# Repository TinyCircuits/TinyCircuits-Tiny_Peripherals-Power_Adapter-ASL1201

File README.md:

# TinyCircuits TinyLily Mini Power Adapter
# ASL1201 Rev2

The design files are located under design_files/ for the TinyCircuits ASL1201 Rev 2 PCB.  This is a TinyLily Mini Power Adapter, that mates to the TinyLily Mini board and has a JST power connector, along with pads to solder to.

Format is in Cadsoft Eagle format - Eagle version 6.2 was used for the original design.

For more infomation on this, check out the product page at TinyCircuits.com: https://tinycircuits.com/collections/tinylily/products/tinylily-battery-adapter

# License:

Design by TinyCircuits.
All design files are released under the Creative Commons Attribution Share-Alike 3.0 License, see the following link for details: http://creativecommons.org/licenses/by-sa/3.0

All text above must be included in any redistribution or derived design

This project uses designs and concepts developed as part of the Arduino project and the LilyPad project.  The TinyCircuits design files themselves (schematics, PCB and libraries) are not directly derived from these works' design files and have been created new, however the concepts and basic architecture behind the TinyDuino and TinyLily products are derived and we thank the hard work of the organizations below for their contributions to open-source hardware:
  
Original Arduino Uno Design by Team Arduino

LilyPad Arduino Design by Leah Buechley and Sparkfun Electronics

Please support the open-source hardware community

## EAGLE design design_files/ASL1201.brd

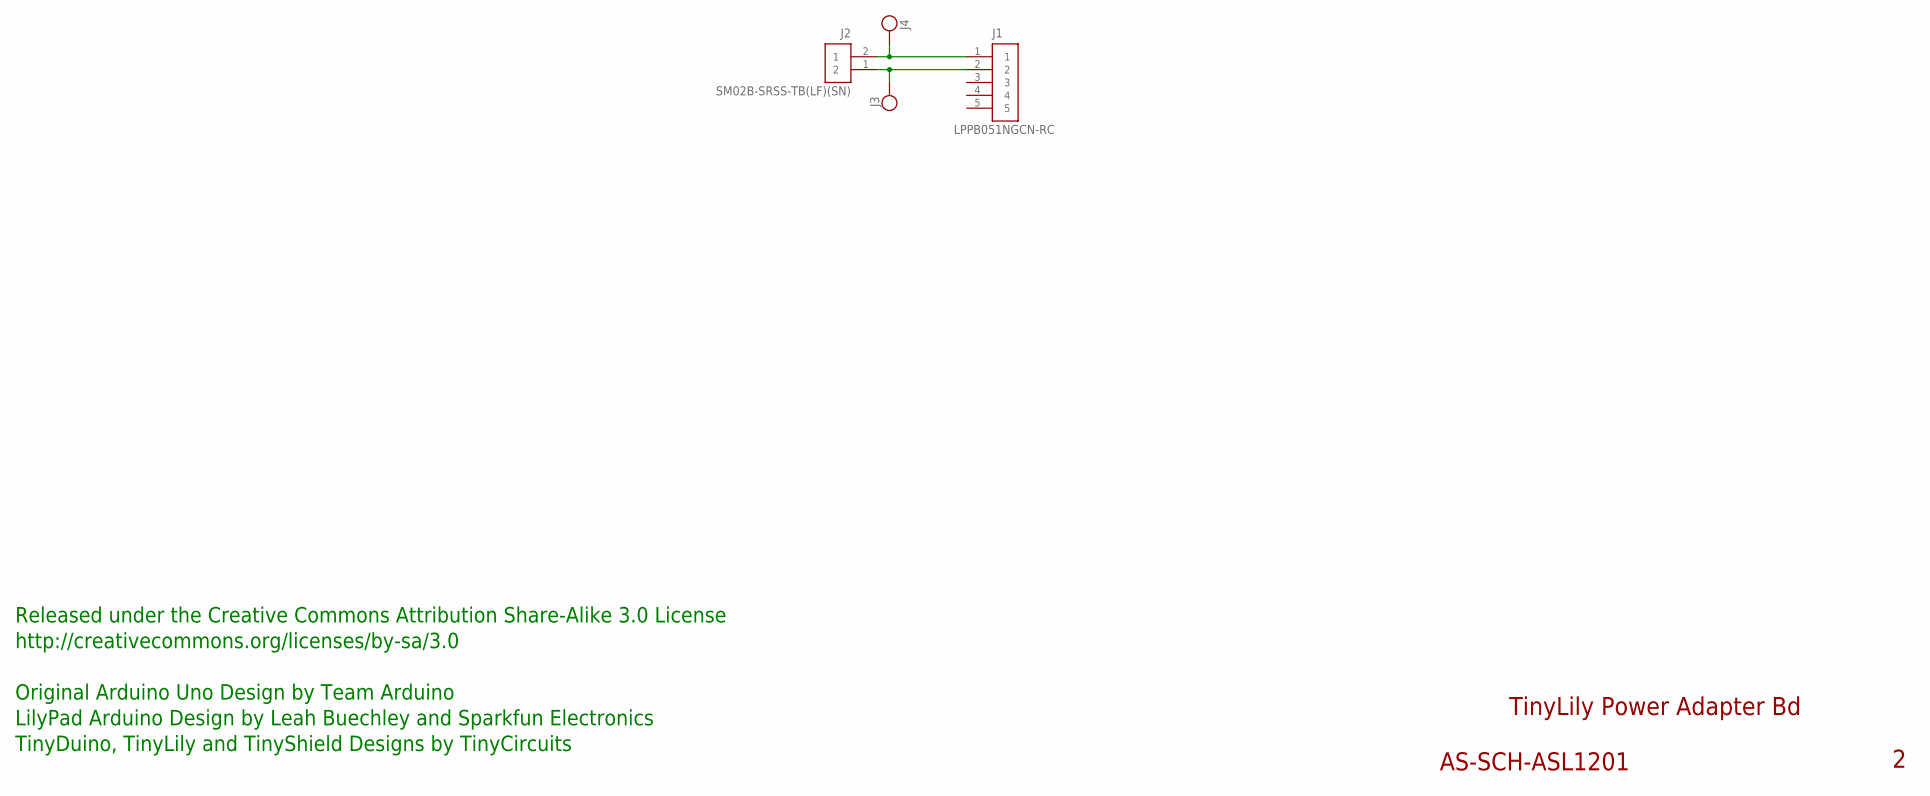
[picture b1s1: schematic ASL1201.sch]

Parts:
J1: LPPB051NGCN-RC; 1X5_.05_RA_TH_RECPT
J2: SM02B-SRSS-TB(LF)(SN); JST_SH_2X1
J3, J4: PIN_1X.1"1; 1X.1"_2

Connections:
unnamed: J1.1, J2.2 (1), J4.1
unnamed: J1.2, J2.1 (2), J3.1

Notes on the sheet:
TinyLily Power Adapter Bd
AS-SCH-ASL1201
Released under the Creative Commons Attribution Share-Alike 3.0 License
http://creativecommons.org/licenses/by-sa/3.0
LilyPad Arduino Design by Leah Buechley and Sparkfun Electronics
TinyDuino, TinyLily and TinyShield Designs by TinyCircuits
Original Arduino Uno Design by Team Arduino

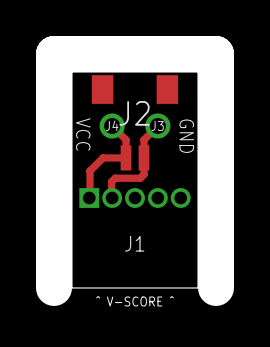
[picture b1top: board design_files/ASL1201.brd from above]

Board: 2 copper layers, 9.0 x 13.0 mm, 5 parts (0 on the bottom side), 2 nets.

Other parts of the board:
U$1: DOCFIELD-TINYCIRCUITS-PCB

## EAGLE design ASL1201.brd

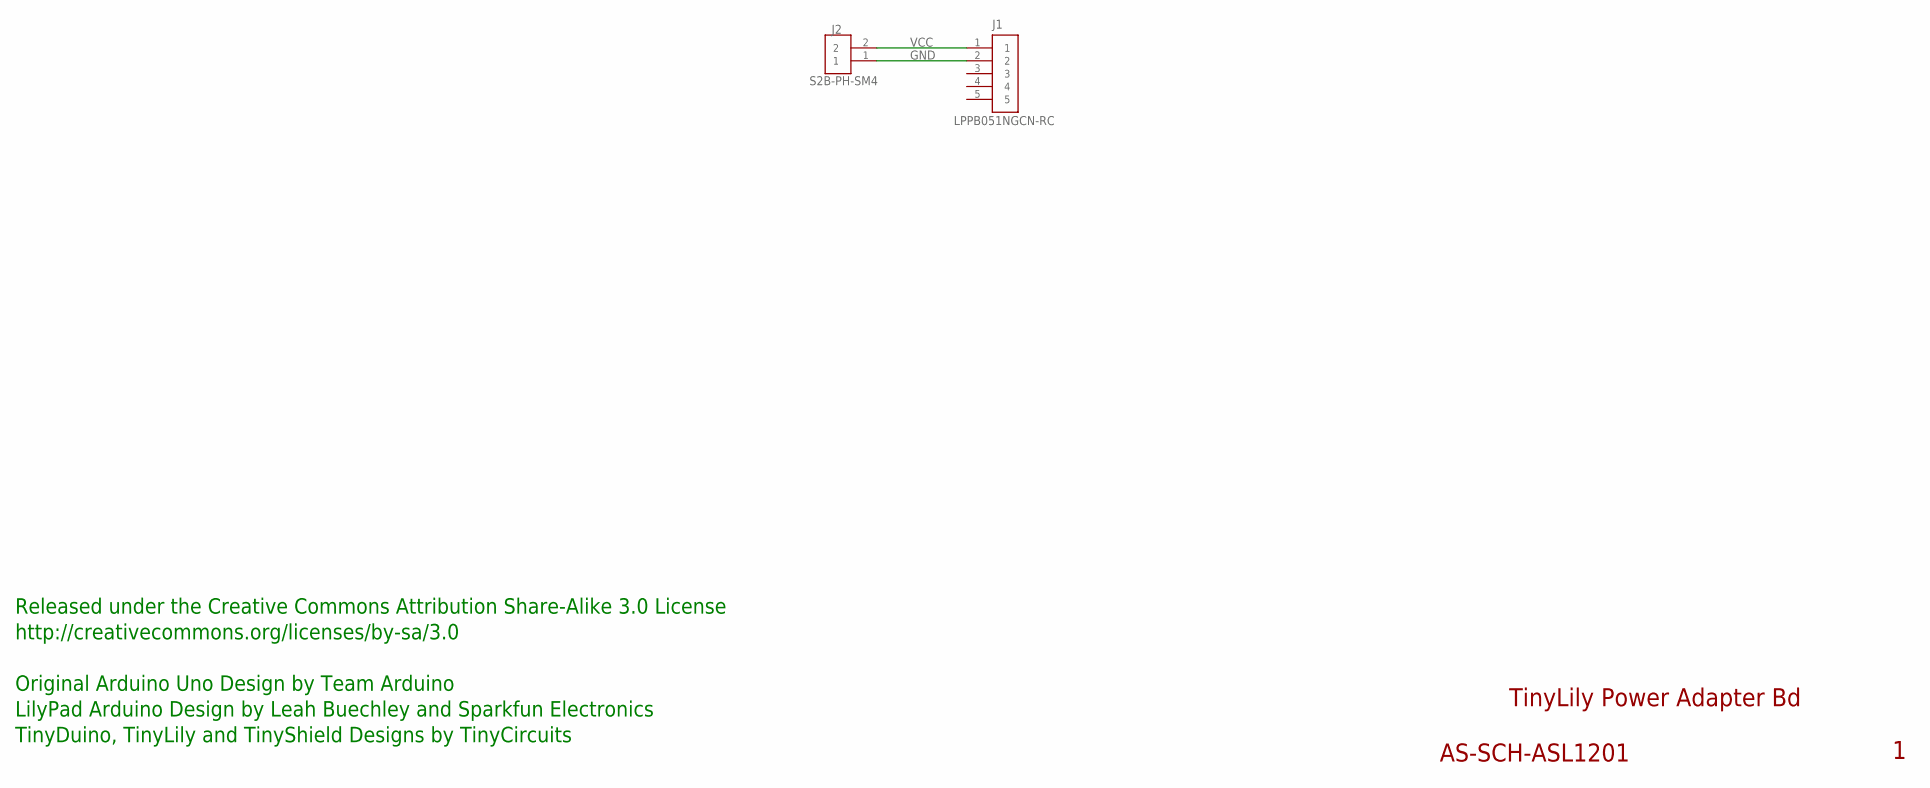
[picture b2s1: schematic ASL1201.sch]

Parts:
J1: LPPB051NGCN-RC; 1X5_.05_RA_TH_RECPT
J2: S2B-PH-SM4; JST_PH_2

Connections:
GND: J1.2, J2.1
VCC: J1.1, J2.2

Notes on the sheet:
TinyLily Power Adapter Bd
AS-SCH-ASL1201
Released under the Creative Commons Attribution Share-Alike 3.0 License
http://creativecommons.org/licenses/by-sa/3.0
LilyPad Arduino Design by Leah Buechley and Sparkfun Electronics
TinyDuino, TinyLily and TinyShield Designs by TinyCircuits
Original Arduino Uno Design by Team Arduino

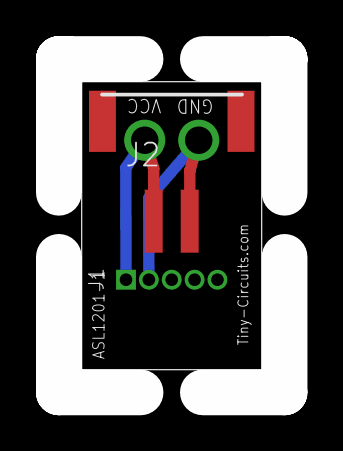
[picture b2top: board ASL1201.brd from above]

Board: 2 copper layers, 10.0 x 16.0 mm, 3 parts (0 on the bottom side), 2 nets.

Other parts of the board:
U$1: DOCFIELD-TINYCIRCUITS-PCB

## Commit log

2012-09-16 Fixed Incorrect Name
2013-06-30 Updated project link
2014-08-24 Updated Link
2019-01-04 update format
2020-08-28 Add CAD data
